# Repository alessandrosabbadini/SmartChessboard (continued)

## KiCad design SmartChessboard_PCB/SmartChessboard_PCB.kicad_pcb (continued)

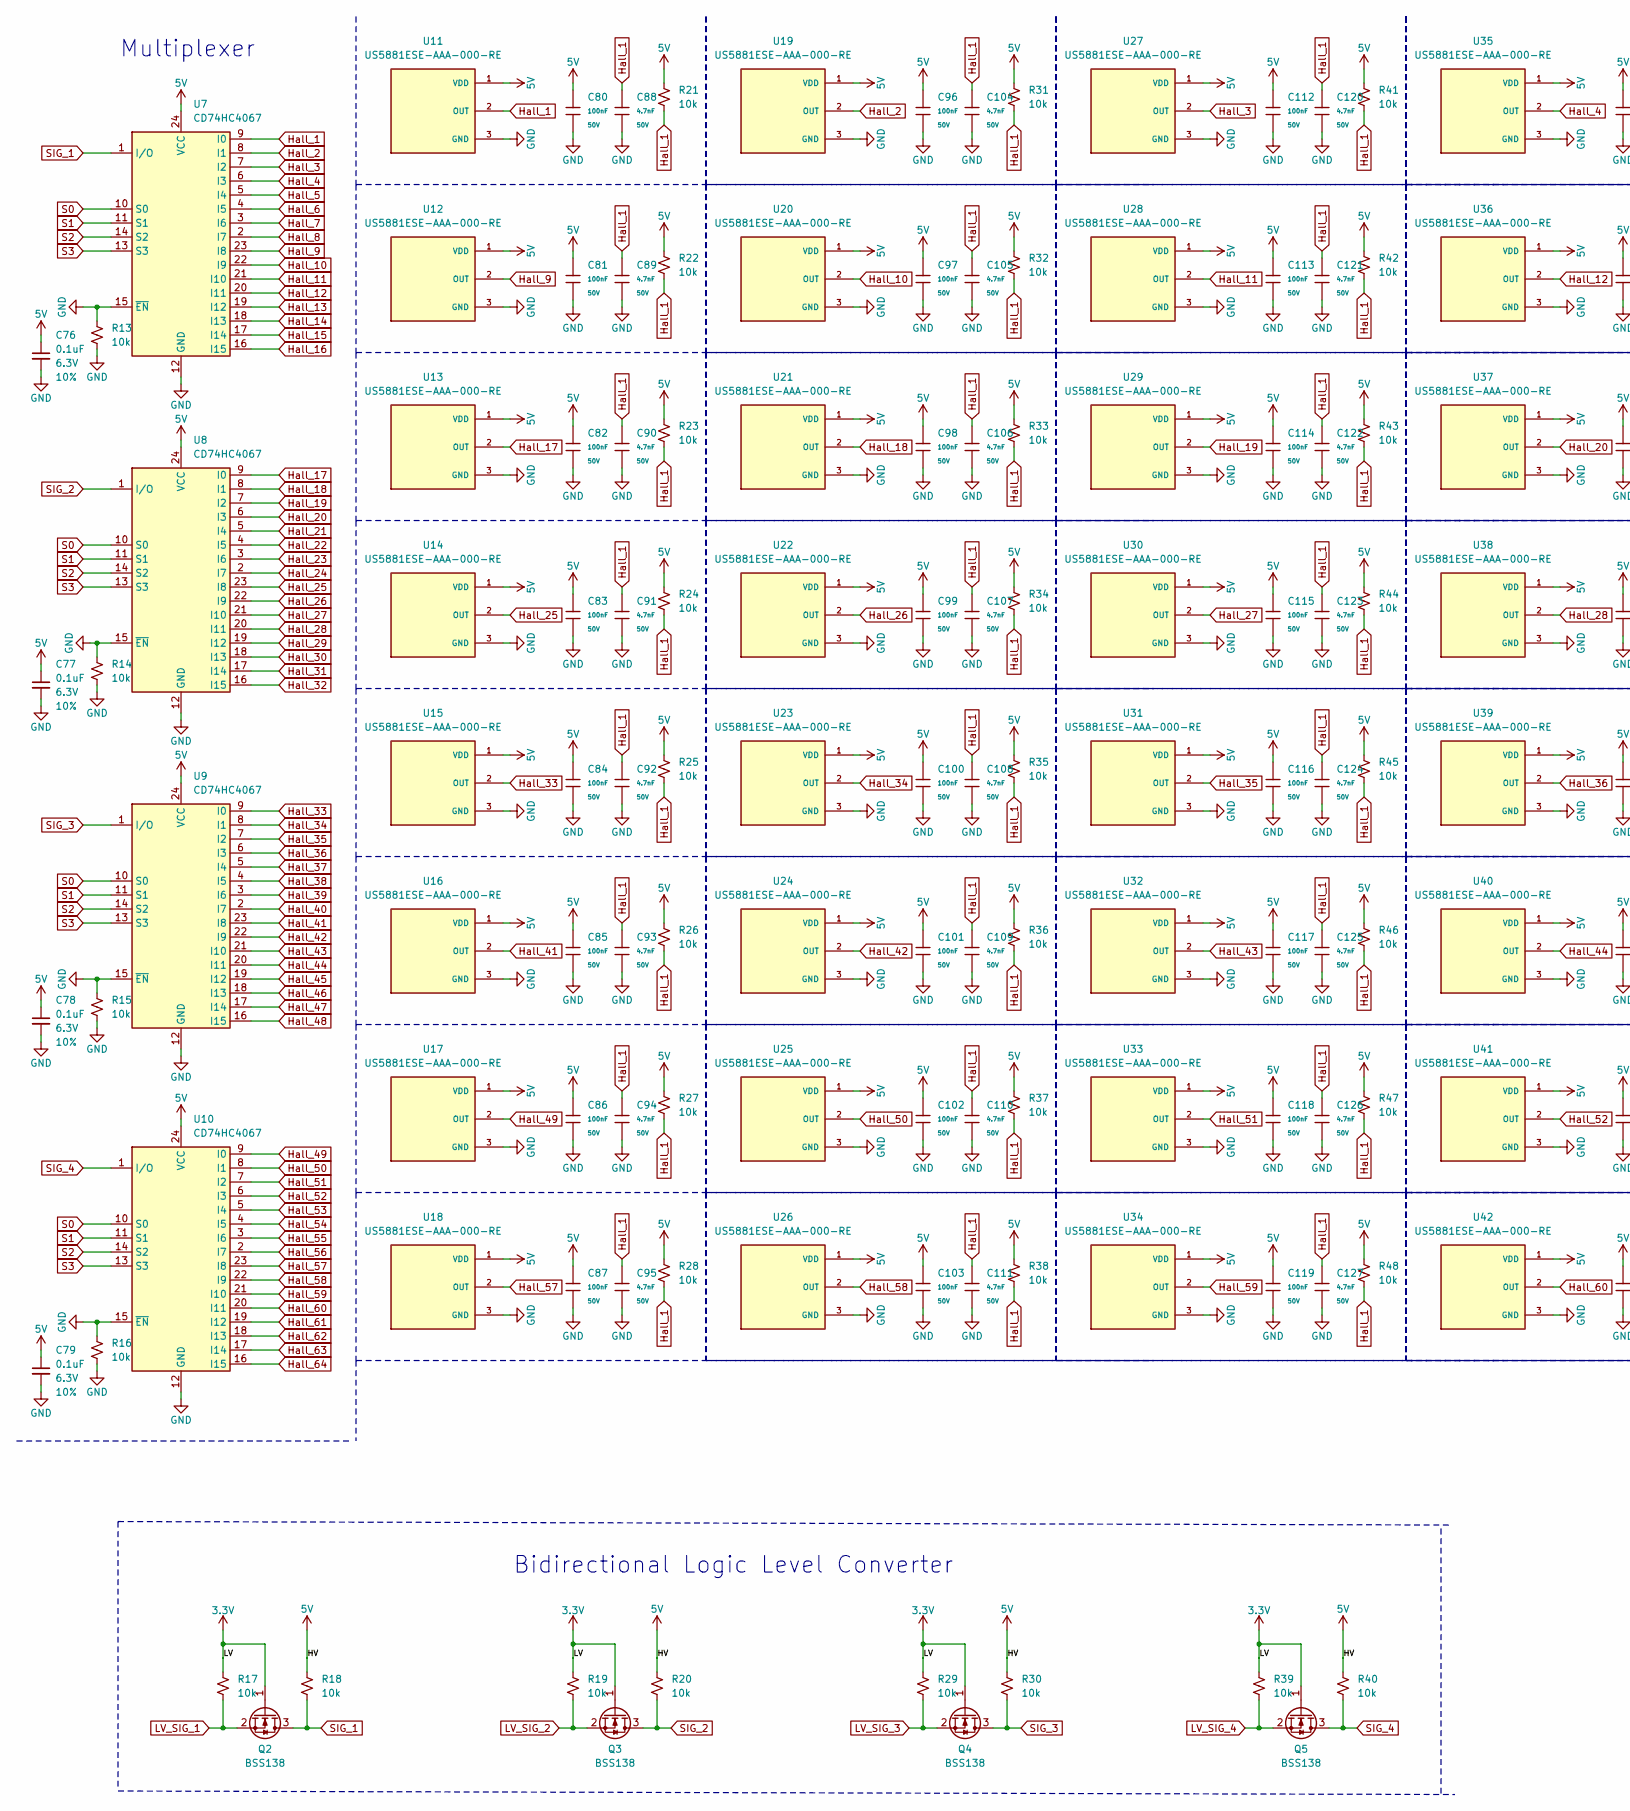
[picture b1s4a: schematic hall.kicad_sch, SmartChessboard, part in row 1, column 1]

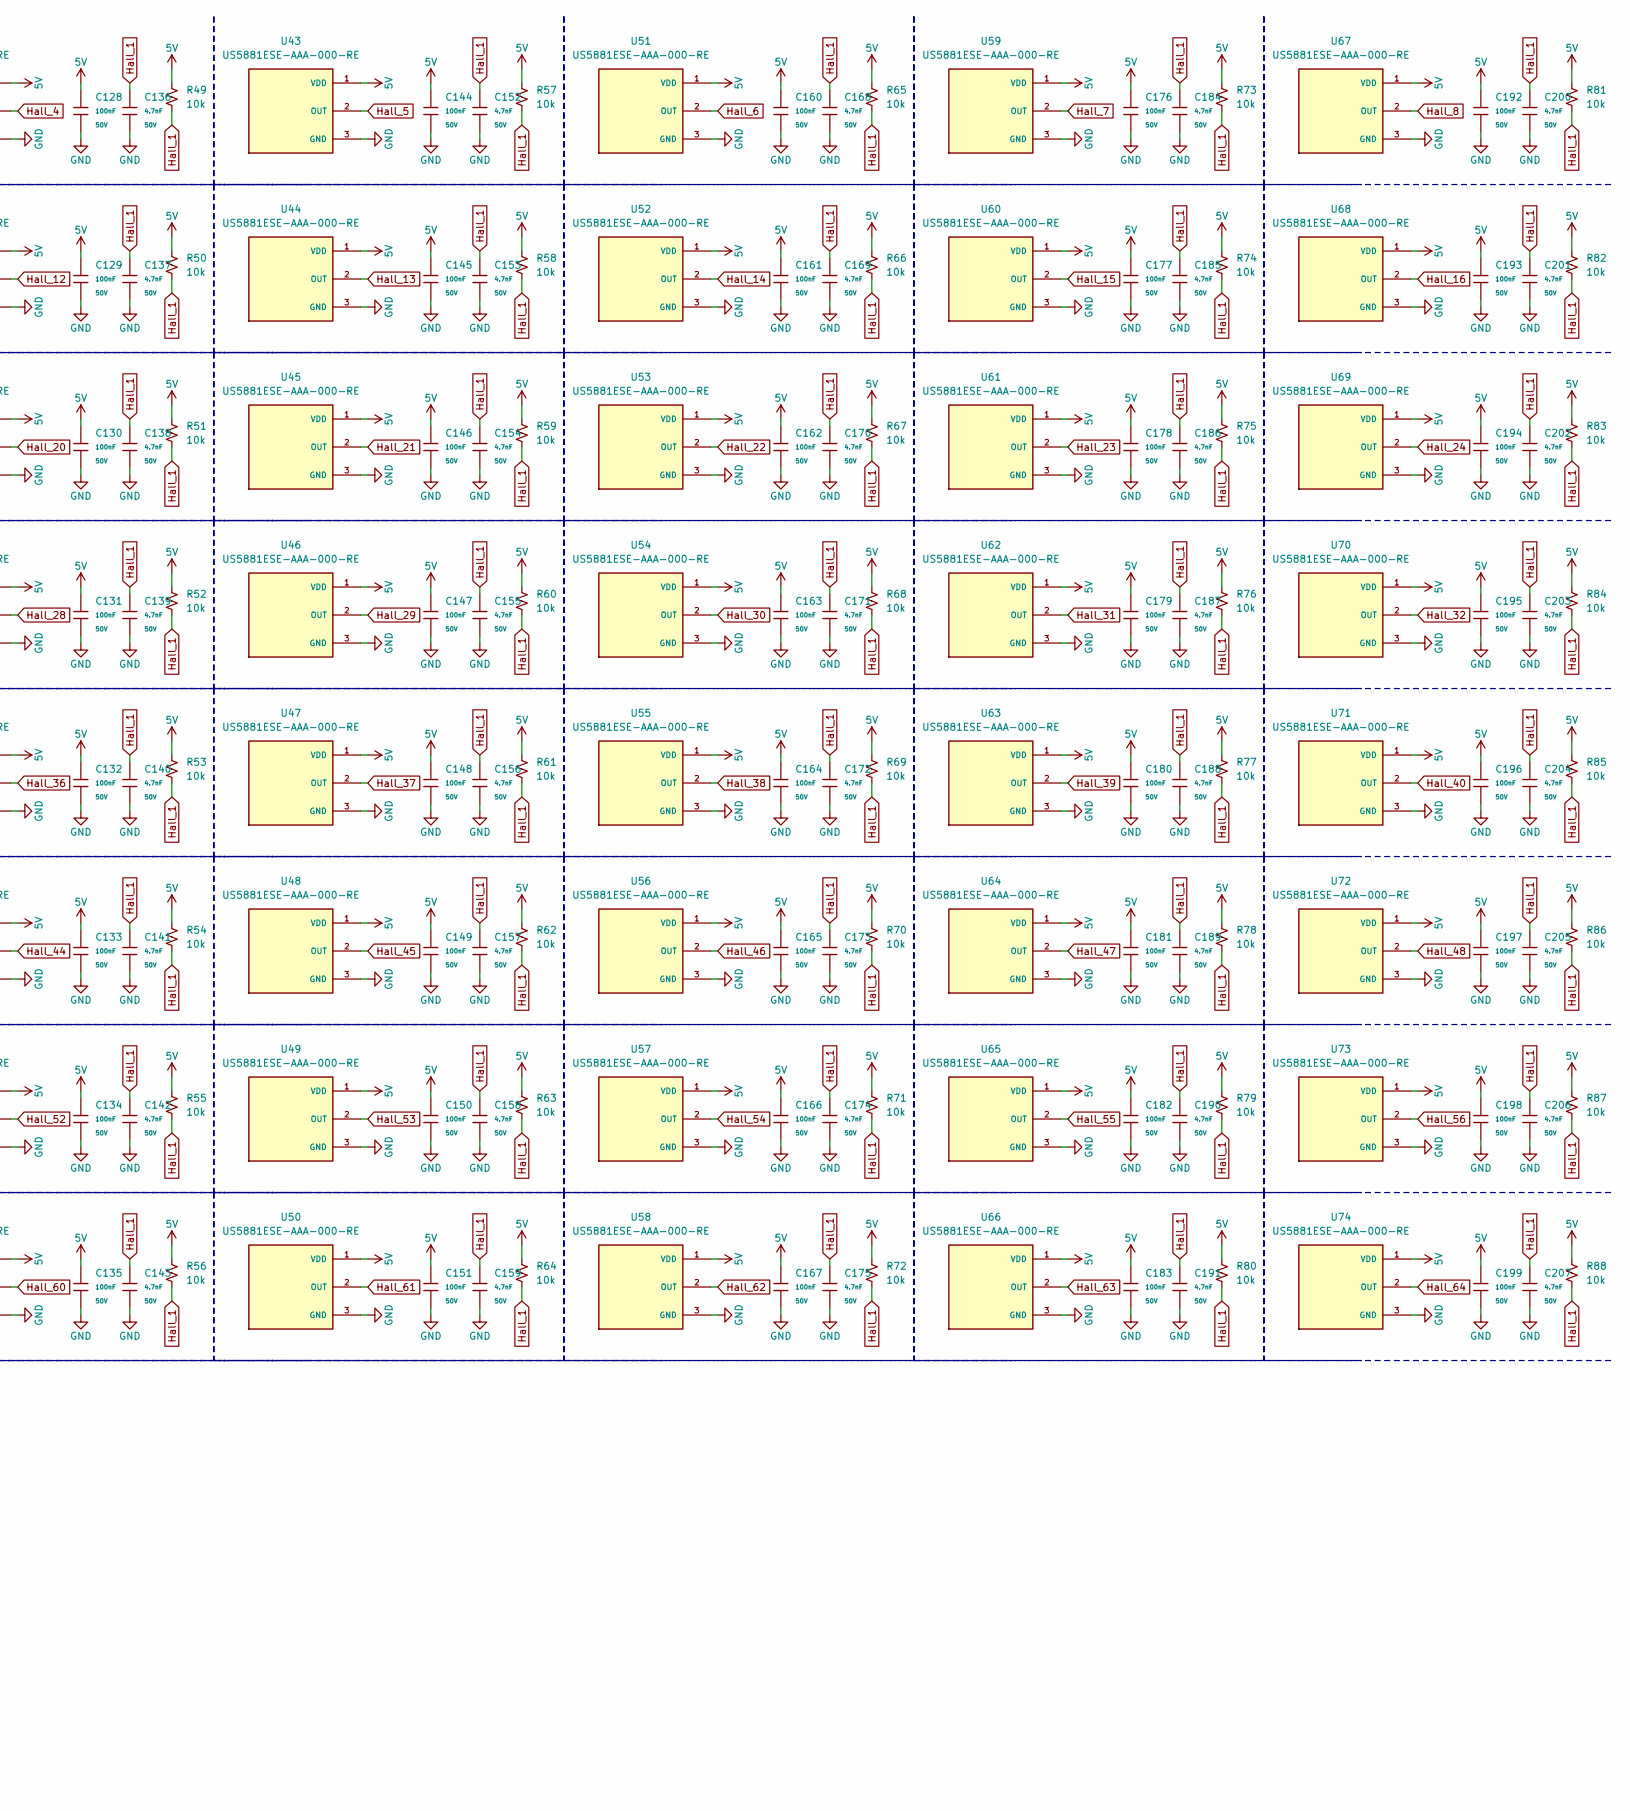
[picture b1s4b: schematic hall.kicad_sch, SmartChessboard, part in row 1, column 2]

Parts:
C76, C77, C78, C79: 0.1uF; C_0402_1005Metric; Voltage 6.3V; Tolerance 10%
C80, C81, C82, C83, C84, C85, C86, C87, C96, C97, C98, C99, C100, C101, C102, C103, C112, C113, C114, C115, C116, C117, C118, C119, C128, C129, C130, C131, C132, C133, C134, C135, C144, C145, C146, C147, C148, C149, C150, C151, C160, C161, C162, C163, C164, C165, C166, C167, C176, C177, C178, C179, C180, C181, C182, C183, C192, C193, C194, C195, C196, C197, C198, C199: 100nF; C_0402; Voltage Rated 50V; Tolerance ±10%; Part CL05B104KB54PNC; LCSC C307331
C88, C89, C90, C91, C92, C93, C94, C95, C104, C105, C106, C107, C108, C109, C110, C111, C120, C121, C122, C123, C124, C125, C126, C127, C136, C137, C138, C139, C140, C141, C142, C143, C152, C153, C154, C155, C156, C157, C158, C159, C168, C169, C170, C171, C172, C173, C174, C175, C184, C185, C186, C187, C188, C189, C190, C191, C200, C201, C202, C203, C204, C205, C206, C207: 4.7nF; C_0402; Voltage Rated 50V; Tolerance ±10%; Part 0402B472K500NT; LCSC C1538
Q2, Q3, Q4, Q5: BSS138; SOT-23
R13, R14, R15, R16, R17, R18, R19, R20, R21, R22, R23, R24, R25, R26, R27, R28, R29, R30, R31, R32, R33, R34, R35, R36, R37, R38, R39, R40, R41, R42, R43, R44, R45, R46, R47, R48, R49, R50, R51, R52, R53, R54, R55, R56, R57, R58, R59, R60, R61, R62, R63, R64, R65, R66, R67, R68, R69, R70, R71, R72, R73, R74, R75, R76, R77, R78, R79, R80, R81, R82, R83, R84, R85, R86, R87, R88: 10k; R_0402_1005Metric
U7, U8, U9, U10: CD74HC4067; TSSOP-24_4.4x7.8mm_P0.65mm
U11, U12, U13, U14, U15, U16, U17, U18, U19, U20, U21, U22, U23, U24, U25, U26, U27, U28, U29, U30, U31, U32, U33, U34, U35, U36, U37, U38, U39, U40, U41, U42, U43, U44, U45, U46, U47, U48, U49, U50, U51, U52, U53, U54, U55, U56, U57, U58, U59, U60, U61, U62, U63, U64, U65, U66, U67, U68, U69, U70, U71, U72, U73, U74: US5881ESE-AAA-000-RE; SOT95P280X100-3N; PARTREV 005

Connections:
3.3V: Q2.1 (G), Q3.1 (G), Q4.1 (G), Q5.1 (G), R17.1, R19.1, R29.1, R39.1; also elsewhere on the board
+5V: C76.1, C77.1, C78.1, C79.1, C80.1, C81.1, C82.1, C83.1, C84.1, C85.1, C86.1, C87.1, C96.1, C97.1, C98.1, C99.1, C100.1, C101.1, C102.1, C103.1, C112.1, C113.1, C114.1, C115.1, C116.1, C117.1, C118.1, C119.1, C128.1, C129.1, C130.1, C131.1, C132.1, C133.1, C134.1, C135.1, C144.1, C145.1, C146.1, C147.1, C148.1, C149.1, C150.1, C151.1, C160.1, C161.1, C162.1, C163.1, C164.1, C165.1, C166.1, C167.1, C176.1, C177.1, C178.1, C179.1, C180.1, C181.1, C182.1, C183.1, C192.1, C193.1, C194.1, C195.1, C196.1, C197.1, C198.1, C199.1, R18.1, R20.1, R21.2, R22.2, R23.2, R24.2, R25.2, R26.2, R27.2, R28.2, R30.1, R31.2, R32.2, R33.2, R34.2, R35.2, R36.2, R37.2, R38.2, R40.1, R41.2, R42.2, R43.2, R44.2, R45.2, R46.2, R47.2, R48.2, R49.2, R50.2, R51.2, R52.2, R53.2, R54.2, R55.2, R56.2, R57.2, R58.2, R59.2, R60.2, R61.2, R62.2, R63.2, R64.2, R65.2, R66.2, R67.2, R68.2, R69.2, R70.2, R71.2, R72.2, R73.2, R74.2, R75.2, R76.2, R77.2, R78.2, R79.2, R80.2, R81.2, R82.2, R83.2, R84.2, R85.2, R86.2, R87.2, R88.2, U7.24 (VCC), U8.24 (VCC), U9.24 (VCC), U10.24 (VCC), U11.1 (VDD), U12.1 (VDD), U13.1 (VDD), U14.1 (VDD), U15.1 (VDD), U16.1 (VDD), U17.1 (VDD), U18.1 (VDD), U19.1 (VDD), U20.1 (VDD), U21.1 (VDD), U22.1 (VDD), U23.1 (VDD), U24.1 (VDD), U25.1 (VDD), U26.1 (VDD), U27.1 (VDD), U28.1 (VDD), U29.1 (VDD), U30.1 (VDD), U31.1 (VDD), U32.1 (VDD), U33.1 (VDD), U34.1 (VDD), U35.1 (VDD), U36.1 (VDD), U37.1 (VDD), U38.1 (VDD), U39.1 (VDD), U40.1 (VDD), U41.1 (VDD), U42.1 (VDD), U43.1 (VDD), U44.1 (VDD), U45.1 (VDD), U46.1 (VDD), U47.1 (VDD), U48.1 (VDD), U49.1 (VDD), U50.1 (VDD), U51.1 (VDD), U52.1 (VDD), U53.1 (VDD), U54.1 (VDD), U55.1 (VDD), U56.1 (VDD), U57.1 (VDD), U58.1 (VDD), U59.1 (VDD), U60.1 (VDD), U61.1 (VDD), U62.1 (VDD), U63.1 (VDD), U64.1 (VDD), U65.1 (VDD), U66.1 (VDD), U67.1 (VDD), U68.1 (VDD), U69.1 (VDD), U70.1 (VDD), U71.1 (VDD), U72.1 (VDD), U73.1 (VDD), U74.1 (VDD); also elsewhere on the board
GND: C76.2, C77.2, C78.2, C79.2, C80.2, C81.2, C82.2, C83.2, C84.2, C85.2, C86.2, C87.2, C88.2, C89.2, C90.2, C91.2, C92.2, C93.2, C94.2, C95.2, C96.2, C97.2, C98.2, C99.2, C100.2, C101.2, C102.2, C103.2, C104.2, C105.2, C106.2, C107.2, C108.2, C109.2, C110.2, C111.2, C112.2, C113.2, C114.2, C115.2, C116.2, C117.2, C118.2, C119.2, C120.2, C121.2, C122.2, C123.2, C124.2, C125.2, C126.2, C127.2, C128.2, C129.2, C130.2, C131.2, C132.2, C133.2, C134.2, C135.2, C136.2, C137.2, C138.2, C139.2, C140.2, C141.2, C142.2, C143.2, C144.2, C145.2, C146.2, C147.2, C148.2, C149.2, C150.2, C151.2, C152.2, C153.2, C154.2, C155.2, C156.2, C157.2, C158.2, C159.2, C160.2, C161.2, C162.2, C163.2, C164.2, C165.2, C166.2, C167.2, C168.2, C169.2, C170.2, C171.2, C172.2, C173.2, C174.2, C175.2, C176.2, C177.2, C178.2, C179.2, C180.2, C181.2, C182.2, C183.2, C184.2, C185.2, C186.2, C187.2, C188.2, C189.2, C190.2, C191.2, C192.2, C193.2, C194.2, C195.2, C196.2, C197.2, C198.2, C199.2, C200.2, C201.2, C202.2, C203.2, C204.2, C205.2, C206.2, C207.2, R13.1, R13.2, R14.1, R14.2, R15.1, R15.2, R16.1, R16.2, U7.12 (GND), U7.15 (~EN), U8.12 (GND), U8.15 (~EN), U9.12 (GND), U9.15 (~EN), U10.12 (GND), U10.15 (~EN), U11.3 (GND), U12.3 (GND), U13.3 (GND), U14.3 (GND), U15.3 (GND), U16.3 (GND), U17.3 (GND), U18.3 (GND), U19.3 (GND), U20.3 (GND), U21.3 (GND), U22.3 (GND), U23.3 (GND), U24.3 (GND), U25.3 (GND), U26.3 (GND), U27.3 (GND), U28.3 (GND), U29.3 (GND), U30.3 (GND), U31.3 (GND), U32.3 (GND), U33.3 (GND), U34.3 (GND), U35.3 (GND), U36.3 (GND), U37.3 (GND), U38.3 (GND), U39.3 (GND), U40.3 (GND), U41.3 (GND), U42.3 (GND), U43.3 (GND), U44.3 (GND), U45.3 (GND), U46.3 (GND), U47.3 (GND), U48.3 (GND), U49.3 (GND), U50.3 (GND), U51.3 (GND), U52.3 (GND), U53.3 (GND), U54.3 (GND), U55.3 (GND), U56.3 (GND), U57.3 (GND), U58.3 (GND), U59.3 (GND), U60.3 (GND), U61.3 (GND), U62.3 (GND), U63.3 (GND), U64.3 (GND), U65.3 (GND), U66.3 (GND), U67.3 (GND), U68.3 (GND), U69.3 (GND), U70.3 (GND), U71.3 (GND), U72.3 (GND), U73.3 (GND), U74.3 (GND); also elsewhere on the board
Hall_1: C88.1, C89.1, C90.1, C91.1, C92.1, C93.1, C94.1, C95.1, C104.1, C105.1, C106.1, C107.1, C108.1, C109.1, C110.1, C111.1, C120.1, C121.1, C122.1, C123.1, C124.1, C125.1, C126.1, C127.1, C136.1, C137.1, C138.1, C139.1, C140.1, C141.1, C142.1, C143.1, C152.1, C153.1, C154.1, C155.1, C156.1, C157.1, C158.1, C159.1, C168.1, C169.1, C170.1, C171.1, C172.1, C173.1, C174.1, C175.1, C184.1, C185.1, C186.1, C187.1, C188.1, C189.1, C190.1, C191.1, C200.1, C201.1, C202.1, C203.1, C204.1, C205.1, C206.1, C207.1, R21.1, R22.1, R23.1, R24.1, R25.1, R26.1, R27.1, R28.1, R31.1, R32.1, R33.1, R34.1, R35.1, R36.1, R37.1, R38.1, R41.1, R42.1, R43.1, R44.1, R45.1, R46.1, R47.1, R48.1, R49.1, R50.1, R51.1, R52.1, R53.1, R54.1, R55.1, R56.1, R57.1, R58.1, R59.1, R60.1, R61.1, R62.1, R63.1, R64.1, R65.1, R66.1, R67.1, R68.1, R69.1, R70.1, R71.1, R72.1, R73.1, R74.1, R75.1, R76.1, R77.1, R78.1, R79.1, R80.1, R81.1, R82.1, R83.1, R84.1, R85.1, R86.1, R87.1, R88.1, U7.9 (I0), U11.2 (OUT)
Hall_2: U7.8 (I1), U19.2 (OUT)
Hall_3: U7.7 (I2), U27.2 (OUT)
Hall_4: U7.6 (I3), U35.2 (OUT)
Hall_5: U7.5 (I4), U43.2 (OUT)
Hall_6: U7.4 (I5), U51.2 (OUT)
Hall_7: U7.3 (I6), U59.2 (OUT)
Hall_8: U7.2 (I7), U67.2 (OUT)
Hall_9: U7.23 (I8), U12.2 (OUT)
Hall_10: U7.22 (I9), U20.2 (OUT)
Hall_11: U7.21 (I10), U28.2 (OUT)
Hall_12: U7.20 (I11), U36.2 (OUT)
Hall_13: U7.19 (I12), U44.2 (OUT)
Hall_14: U7.18 (I13), U52.2 (OUT)
Hall_15: U7.17 (I14), U60.2 (OUT)
Hall_16: U7.16 (I15), U68.2 (OUT)
Hall_17: U8.9 (I0), U13.2 (OUT)
Hall_18: U8.8 (I1), U21.2 (OUT)
Hall_19: U8.7 (I2), U29.2 (OUT)
Hall_20: U8.6 (I3), U37.2 (OUT)
Hall_21: U8.5 (I4), U45.2 (OUT)
Hall_22: U8.4 (I5), U53.2 (OUT)
Hall_23: U8.3 (I6), U61.2 (OUT)
Hall_24: U8.2 (I7), U69.2 (OUT)
Hall_25: U8.23 (I8), U14.2 (OUT)
Hall_26: U8.22 (I9), U22.2 (OUT)
Hall_27: U8.21 (I10), U30.2 (OUT)
Hall_28: U8.20 (I11), U38.2 (OUT)
Hall_29: U8.19 (I12), U46.2 (OUT)
Hall_30: U8.18 (I13), U54.2 (OUT)
Hall_31: U8.17 (I14), U62.2 (OUT)
Hall_32: U8.16 (I15), U70.2 (OUT)
Hall_33: U9.9 (I0), U15.2 (OUT)
Hall_34: U9.8 (I1), U23.2 (OUT)
Hall_35: U9.7 (I2), U31.2 (OUT)
Hall_36: U9.6 (I3), U39.2 (OUT)
Hall_37: U9.5 (I4), U47.2 (OUT)
Hall_38: U9.4 (I5), U55.2 (OUT)
Hall_39: U9.3 (I6), U63.2 (OUT)
Hall_40: U9.2 (I7), U71.2 (OUT)
Hall_41: U9.23 (I8), U16.2 (OUT)
Hall_42: U9.22 (I9), U24.2 (OUT)
Hall_43: U9.21 (I10), U32.2 (OUT)
Hall_44: U9.20 (I11), U40.2 (OUT)
Hall_45: U9.19 (I12), U48.2 (OUT)
Hall_46: U9.18 (I13), U56.2 (OUT)
Hall_47: U9.17 (I14), U64.2 (OUT)
Hall_48: U9.16 (I15), U72.2 (OUT)
Hall_49: U10.9 (I0), U17.2 (OUT)
Hall_50: U10.8 (I1), U25.2 (OUT)
Hall_51: U10.7 (I2), U33.2 (OUT)
Hall_52: U10.6 (I3), U41.2 (OUT)
Hall_53: U10.5 (I4), U49.2 (OUT)
Hall_54: U10.4 (I5), U57.2 (OUT)
Hall_55: U10.3 (I6), U65.2 (OUT)
Hall_56: U10.2 (I7), U73.2 (OUT)
Hall_57: U10.23 (I8), U18.2 (OUT)
Hall_58: U10.22 (I9), U26.2 (OUT)
Hall_59: U10.21 (I10), U34.2 (OUT)
Hall_60: U10.20 (I11), U42.2 (OUT)
Hall_61: U10.19 (I12), U50.2 (OUT)
Hall_62: U10.18 (I13), U58.2 (OUT)
Hall_63: U10.17 (I14), U66.2 (OUT)
Hall_64: U10.16 (I15), U74.2 (OUT)
LV_SIG_1: Q2.2 (S), R17.2; also elsewhere on the board
LV_SIG_2: Q3.2 (S), R19.2; also elsewhere on the board
LV_SIG_3: Q4.2 (S), R29.2; also elsewhere on the board
LV_SIG_4: Q5.2 (S), R39.2; also elsewhere on the board
S0: U7.10 (S0), U8.10 (S0), U9.10 (S0), U10.10 (S0); also elsewhere on the board
S1: U7.11 (S1), U8.11 (S1), U9.11 (S1), U10.11 (S1); also elsewhere on the board
S2: U7.14 (S2), U8.14 (S2), U9.14 (S2), U10.14 (S2); also elsewhere on the board
S3: U7.13 (S3), U8.13 (S3), U9.13 (S3), U10.13 (S3); also elsewhere on the board
SIG_1: Q2.3 (D), R18.2, U7.1 (I/O)
SIG_2: Q3.3 (D), R20.2, U8.1 (I/O)
SIG_3: Q4.3 (D), R30.2, U9.1 (I/O)
SIG_4: Q5.3 (D), R40.2, U10.1 (I/O)

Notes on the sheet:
Bidirectional Logic Level Converter
Multiplexer

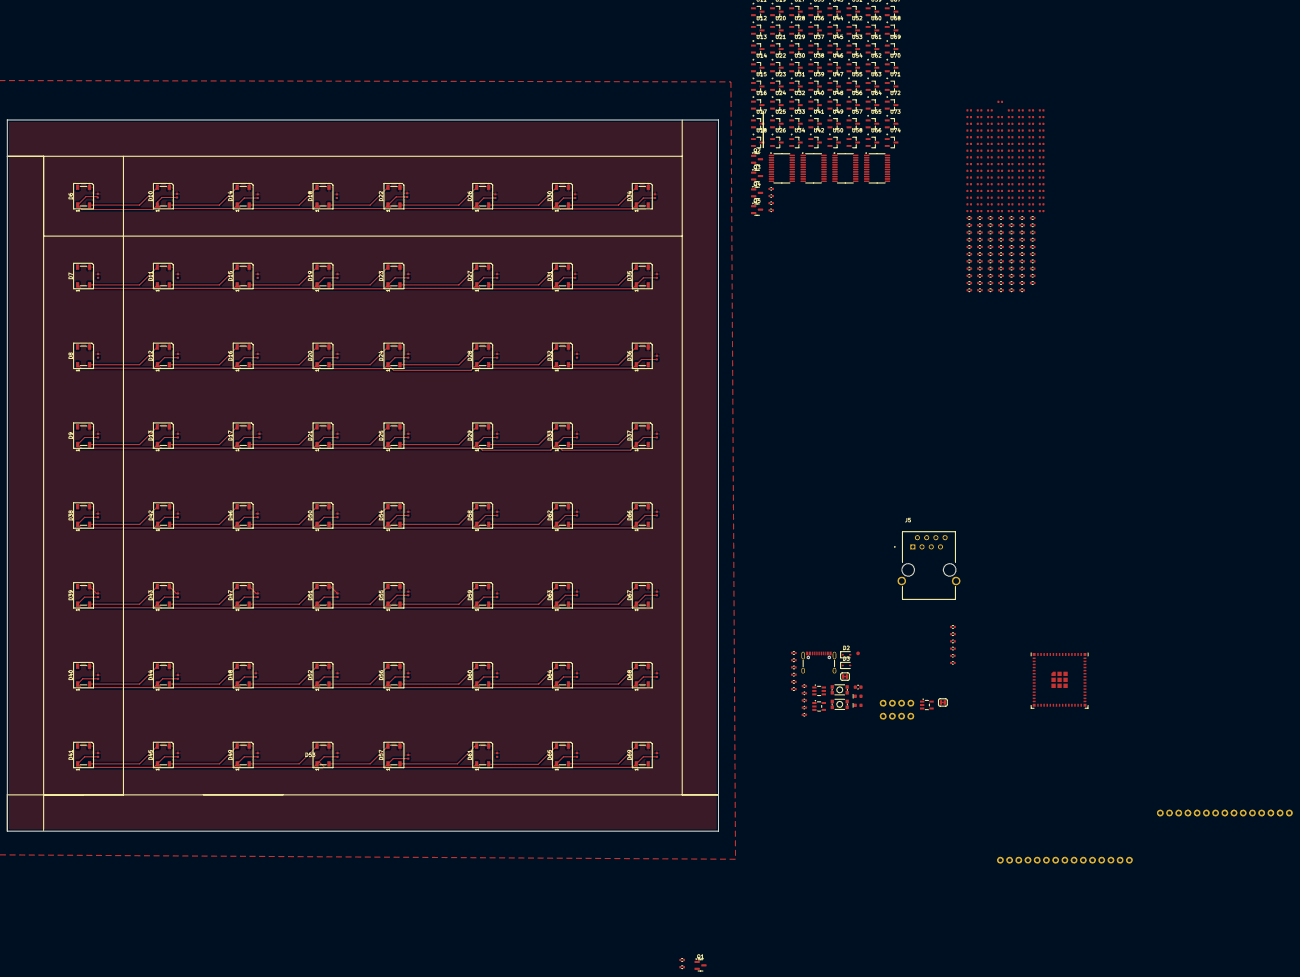
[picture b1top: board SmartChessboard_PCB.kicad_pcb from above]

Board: 2 copper layers, 196.0 x 196.0 mm, 449 parts (0 on the bottom side), 184 nets.

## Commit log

2025-08-24 Update LICENSE
2025-08-24 Createc Kicad file
2025-08-24 Folder renamed
2025-08-25 first test
2025-08-28 28/08/25
2025-08-28 DSstore
2025-08-28 Remove .DS_Store files from repo
2025-08-29 esp32-s3 added
2025-09-01 LEDs added
2025-09-01 before hall sensors
2025-09-03 level shifter added
2025-09-15 added pwr management pcb
2025-09-16 pcb finished
2025-09-20 firmware connecting to wifi
